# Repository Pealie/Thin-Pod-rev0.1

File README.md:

# Thin-Pod rev 0.1

<p align="left">
  
</p>
<p align="left">
  <strong>OSHWA Certified Open Source Hardware · UK000091</strong><br>
  Certified 28 May 2026 · <a href="https://certification.oshwa.org/uk000091.html">View certification record</a>
</p>

## Overview

Thin-Pod rev 0.1 is a compact analogue vibration-sensing carrier board intended for experimental condition-monitoring work on motors, pumps, fans, gearboxes and similar rotating machinery. The board supports an ADXL1005-based analogue accelerometer signal path and provides protected power entry, a regulated and switched sensor supply, signal conditioning, accessible test points and a mating interface for a commercially supplied Qorvo DWM3001-CDK development board.

The design is published as an open-hardware PCB release: editable KiCad source files, project-local library files, fabrication outputs, bill of materials and verification documentation are provided in this repository.

The release is intentionally bounded: its value lies in producing a reproducible, inspectable measurement endpoint whose power path, signal path, interface assumptions and validation evidence can support later Gateway-side analysis, reporting and evaluation work within a clearly defined certified hardware boundary.

## Certification scope

The OSHWA certification for **Thin-Pod rev 0.1** covers the creator-designed sensor-node carrier PCB and its release documentation.

### Included in scope

* Two-layer Thin-Pod carrier PCB design.
* Protected power-entry path, fuse provision and reverse-polarity protection.
* Regulated 3.3 V power path and PFET-switched accelerometer supply.
* ADXL1005 analogue sensor interface and conditioned signal path.
* Electrical test points for bring-up and measurement.
* Thin-Pod-authored mating interface for a Qorvo DWM3001-CDK.
* Corrected carrier-board ground return for the DWM3001-CDK interface.
* Editable KiCad source files, fabrication outputs, BOM and documentation.

### Outside scope

* The Qorvo DWM3001-CDK itself as open hardware.
* The Analog Devices ADXL1005 device or any vendor evaluation board as open hardware.
* The Pololu S7V8F3 regulator module as open hardware.
* The separately developed Thin-Pod Gateway.
* STM32 NUCLEO-N657X0-Q, ESP32-C6 or Gateway-side hardware.
* Implemented UWB communication, radio firmware or networking.
* Gateway-side DSP, TinyML inference, anomaly detection or predictive-maintenance classification.
* AI-assisted maintenance reporting, structured evidence-bound reports or autonomous maintenance decisions.

The commercial devices used by the board are identified as third-party components; they are not relicensed or represented as creator-designed open hardware.

## System role and infrastructure context

Thin-Pod rev 0.1 is the sensing-node hardware layer within a broader experimental condition-monitoring architecture. Its immediate role is to provide a reproducible, inspectable and electrically verified vibration-measurement endpoint for motors, pumps, fans, gearboxes and similar rotating machinery.

```
Machine / motor / pump
        ↓
Thin-Pod rev 0.1 sensing node
        ↓
ADC / UWB-capable commercial module interface
        ↓
Gateway transport and analysis layer
        ↓
Maintenance telemetry / diagnostic workflow
```

The infrastructure concerns addressed by this release are measurement integrity, power-path robustness, interface definition, third-party component boundaries, traceable validation evidence and manufacturable open-hardware documentation.

Only the Thin-Pod rev 0.1 sensing-node carrier PCB and its release documentation are included in the certified open-hardware scope. The ADC-capable commercial module interface is documented as part of the board design, but the commercial module itself is not claimed as open hardware.

Gateway transport, UWB communications, networking, DSP, TinyML, anomaly detection and maintenance-diagnostic workflows are shown here to clarify the intended system context. They are part of the wider Thin-Pod development direction, but remain outside the certified rev 0.1 hardware release.

This boundary is deliberate. Thin-Pod rev 0.1 is designed to make the physical measurement layer explicit before higher-level interpretation is attempted. Later Gateway or software layers can consume the resulting signal path, but any DSP, anomaly detection, AI-assisted reporting or maintenance recommendation must remain separately implemented, evaluated and documented.

## Functional architecture

```text
Mechanical vibration
        ↓
ADXL1005 analogue accelerometer interface
        ↓
Analogue conditioning / filtered signal node
        ↓
Accessible test point and CDK ADC interface
        ↓
Commercial Qorvo DWM3001-CDK connection
```

Power is arranged as:

```text
RAW_IN → fuse provision → 1N5817 reverse-polarity protection
       → Pololu S7V8F3 regulated 3.3 V rail
       → PFET-switched accelerometer supply
```

## Evidence-chain design intent

Thin-Pod rev 0.1 is intended to support an evidence-chain approach to experimental condition monitoring. The carrier board provides the physical sensing and interface layer; later Gateway-side work may attach acquisition metadata, operating-context records, DSP feature outputs, baseline comparisons and report provenance.

In that wider architecture, the hardware layer should remain distinct from any interpretive software layer. The board records or exposes a vibration signal; it does not itself diagnose machine faults. This separation is important for reproducibility, safety, evaluation and possible future AI-assisted reporting workflows.

## DWM3001-CDK ground-return correction

During bring-up of an earlier pre-release manufactured prototype, the CDK did not establish the assumed functional ground return through the original power-entry arrangement alone. A temporary ground jumper allowed successful electrical bring-up and measurement of the sensor path.

Before freezing the rev 0.1 open-hardware release, the CDK mating interface and carrier-board connection were corrected so that all relevant CDK ground connections resolve directly to the Thin-Pod `GND` net:

```text
J1_2    GND    ─┐
J1_6    GND_1  ─┤
J10_9   GND_2  ─┤
J10_14  GND_3  ─┼── GND
J10_20  GND_4  ─┤
J10_25  GND_5  ─┘
```

The editable source and fabrication outputs in this repository include that correction. The temporary jumper is part of the prototype history and is **not** an assembly requirement for the released rev 0.1 design.

## Validation status

The first manufactured pre-release prototype established that the core sensor-node approach is electrically viable. Measurements made during prototype bring-up included:

|Validation item|Result|Evidence status|
|-|-|-|
|Manufactured PCB inspection and initial assembly|Completed|Documented in bring-up record and images|
|Power-up after temporary CDK ground-return correction|Successful|Documented prototype result|
|Switched accelerometer supply rail|Approximately 3.35 V measured|Documented prototype result|
|Filtered analogue sensor output|Approximately 1.76 V measured at rest|Documented prototype result|
|Mechanical excitation / tap response|Visible on oscilloscope|Documented prototype result|
|Ground-return correction implemented in released KiCad source and Gerbers|Completed|Included in this release|
|Physical re-test of the corrected copper implementation without jumper|To be recorded after manufacture of the corrected release board|Not claimed as completed|

The prototype measurement evidence supports the power and analogue signal-chain design. The corrected ground-return implementation is present in the released design files; it is not represented as physically re-tested until a board manufactured from these release Gerbers has been assembled and measured.

## Repository contents

```text
Thin-Pod-rev0.1/
├── README.md
├── LICENCE-HARDWARE.md
├── LICENCE-DOCUMENTATION.md
│
├── hardware/
│   ├── source/
│   │   ├── Thin-Pod_rev0.1.kicad_pro
│   │   ├── Thin-Pod_rev0.1.kicad_sch
│   │   ├── Thin-Pod_rev0.1.kicad_pcb
│   │   ├── fp-lib-table
│   │   ├── sym-lib-table
│   │   ├── footprints/
│   │   │   └── ThinPod.pretty/
│   │   │       └── ThinPod_DWM3001CDK_Mating_Interface_revA.kicad_mod
│   │   └── symbols/
│   │       └── ThinPod.kicad_sym
│   │
│   ├── fabrication/
│   │   ├── gerbers/
│   │   ├── drills/
│   │   └── Thin-Pod_rev0.1_fabrication_outputs.zip
│   │
│   └── bom/
│       ├── Thin-Pod_rev0.1_BOM.md
│       └── Thin-Pod_rev0.1_BOM.csv
│
├── docs/
│   ├── certification-scope.md
│   ├── third-party-components.md
│   ├── footprint-provenance.md
│   ├── prototype-bring-up-and-release-correction.md
│   ├── design-verification.md
│   └── future-revisions.md
│
├── images/
│   ├── certification/
│   │   └── oshwa-uk000091.png
│   ├── prototype-bring-up/
│   ├── gerber-inspection/
│   └── released-design/
│	└── README.md
│
└── oshwa/
    └── application-record.md
    └── README.md
```

## Design and fabrication files

|Resource|Location|Purpose|
|-|-|-|
|Editable KiCad project, schematic and PCB|[`hardware/source/`](hardware/source/)|Preferred source for modification|
|Project-local footprints and symbols|[`hardware/source/`](hardware/source/)|Portable project dependencies|
|Gerber and drill files|[`hardware/fabrication/`](hardware/fabrication/)|PCB fabrication outputs|
|Bill of materials|[`hardware/bom/`](hardware/bom/)|Assembly and sourcing record|
|Certification and design documentation|[`docs/`](docs/)|Scope, provenance and validation record|
|OSHWA application and certification record|[`oshwa/application-record.md`](oshwa/application-record.md)|Public submission details and certification UID|

The editable KiCad source files are the normative design source. Gerbers and drill files are derived fabrication outputs supplied for convenience and reproducibility.

## Bill of materials

The release BOM covers the Thin-Pod rev 0.1 sensor-node carrier board only. It identifies the fitted PCB components, commercial subassemblies, component values, footprints and sourcing information required to reproduce this release.

The Gateway, Gateway-side radio components, ESP32 networking hardware and analytic processing hardware are not part of this BOM because they are outside the rev 0.1 certification scope.

See:

* [`hardware/bom/Thin-Pod_rev0.1_BOM.md`](hardware/bom/Thin-Pod_rev0.1_BOM.md)
* [`hardware/bom/Thin-Pod_rev0.1_BOM.csv`](hardware/bom/Thin-Pod_rev0.1_BOM.csv)

## Third-party components

Thin-Pod rev 0.1 is an open carrier-board design built around commercially available components. The following items are used or interfaced by the design but are not claimed as open-hardware contributions of this project:

|Component|Function in Thin-Pod rev 0.1|Treatment in this release|
|-|-|-|
|Analog Devices ADXL1005-based accelerometer implementation|Analogue vibration sensing|Commercial third-party component; interface documented|
|Qorvo DWM3001-CDK|Commercial module connected through the pod-side mating interface|Commercial third-party development board; not relicensed|
|Pololu S7V8F3|Regulated 3.3 V supply module|Commercial third-party module|
|ZVP2106A and standard passive/protection components|Power switching and analogue support circuitry|Commercial bought-in components identified in BOM|

Vendor documentation is referenced for sourcing and interface understanding; vendor CAD files, proprietary board layouts and vendor 3D models are not distributed under the Thin-Pod hardware licence.

## CDK mating-interface footprint provenance

The published footprint:

```text
hardware/source/footprints/ThinPod.pretty/
└── ThinPod_DWM3001CDK_Mating_Interface_revA.kicad_mod
```

is a Thin-Pod project-local mating-interface footprint for the commercially supplied DWM3001-CDK. It is intended to describe only the mechanical and electrical connection required by the Thin-Pod carrier PCB.

The release footprint was independently constructed in KiCad using standard connector geometry, publicly available interface information and mechanical verification against a purchased CDK unit. It does not distribute a Qorvo-supplied CAD footprint, CDK PCB design or vendor 3D model.

## Opening and modifying the design

The source design is maintained in KiCad 10.0.1. The project is intended to be portable through project-local symbol and footprint tables.

A reproducible modification workflow is:

1. Open `hardware/source/Thin-Pod_rev0.1.kicad_pro` in KiCad 10.0.1 or a compatible later version.
2. Confirm that project-local symbol and footprint libraries resolve through `sym-lib-table` and `fp-lib-table`.
3. Run schematic ERC and PCB DRC before fabrication.
4. Regenerate Gerber and drill outputs after any accepted design change.
5. Inspect copper, solder mask, silkscreen, board outline and drill alignment in KiCad Gerber Viewer before ordering.

## Documentation and verification record

|Document|Content|
|-|-|
|[`docs/certification-scope.md`](docs/certification-scope.md)|Formal inclusion and exclusion boundary for certification|
|[`docs/third-party-components.md`](docs/third-party-components.md)|Commercial component and vendor-material notice|
|[`docs/footprint-provenance.md`](docs/footprint-provenance.md)|Origin and verification of the CDK mating-interface footprint|
|[`docs/prototype-bring-up-and-release-correction.md`](docs/prototype-bring-up-and-release-correction.md)|Prototype test result and ground-return design correction|
|[`docs/design-verification.md`](docs/design-verification.md)|Electrical and fabrication verification record|
|[`docs/future-revisions.md`](docs/future-revisions.md)|Items explicitly outside this release|

## Licensing

|Material|Licence|File|
|-|-|-|
|Creator-designed hardware source, including schematics, PCB layout and Thin-Pod-authored footprint files|CERN Open Hardware Licence Version 2 — Weakly Reciprocal (`CERN-OHL-W-2.0`)|[`LICENCE-HARDWARE.md`](LICENCE-HARDWARE.md)|
|Creator-authored documentation, diagrams and photographs|Creative Commons Attribution 4.0 International (`CC-BY-4.0`)|[`LICENCE-DOCUMENTATION.md`](LICENCE-DOCUMENTATION.md)|
|Software / firmware|None required or supplied for the certified rev 0.1 hardware scope|Not applicable|

Commercial components, vendor documentation and any third-party intellectual property remain subject to their respective owners' terms and are not covered by the Thin-Pod licences. The OSHWA certification mark is used to identify this certified release and is not relicensed as Thin-Pod documentation.

## OSHWA certification record

**Thin-Pod rev 0.1 is certified open source hardware under OSHWA UID UK000091.** The certification mark displayed near the top of this README identifies this specific certified release and links to the public OSHWA record.

|Field|Value|
|-|-|
|Project name|Thin-Pod|
|Project version|0.1|
|Primary project type|Electronics|
|Certification scope|Vibration-sensor node carrier PCB|
|Certification date|28 May 2026|
|Hardware licence|CERN-OHL-W-2.0|
|Documentation licence|CC-BY-4.0|
|Software licence|No software required or supplied for the certified hardware scope|
|OSHWA UID|UK000091|
|Official record|[certification.oshwa.org/uk000091](https://certification.oshwa.org/uk000091.html)|

The certification UID and matching mark are retained in this README and in [`oshwa/application-record.md`](oshwa/application-record.md), keeping the boundary of the certified rev 0.1 release explicit.

## Safety and regulatory note

Thin-Pod rev 0.1 is experimental sensing hardware. It has not been certified for installation on safety-critical machinery, hazardous environments or regulated industrial monitoring applications. Appropriate isolation, current-limited bench testing, secure mechanical mounting and safe working practices are required during evaluation.

This open-hardware release does not imply EMC, radio, electrical-safety or product-regulatory approval. Any commercially supplied radio or development module remains subject to its own vendor documentation and applicable regulatory conditions.

## References

* [Thin-Pod OSHWA Certification Record — UK000091](https://certification.oshwa.org/uk000091.html)
* [OSHWA Certification Mark Usage Guide](https://certification.oshwa.org/mark-usage.html)
* [OSHWA Certification Requirements](https://certification.oshwa.org/requirements.html)
* [OSHWA Certification Documentation Process](https://certification.oshwa.org/process/documentation.html)
* [OSHWA Certification Application](https://application.oshwa.org/apply)
* [Qorvo DWM3001-CDK product page](https://www.qorvo.com/products/p/DWM3001CDK)
* [Analog Devices ADXL1005 product page](https://www.analog.com/en/products/adxl1005.html)

---

**Thin-Pod rev 0.1** is a deliberately bounded first open-hardware release: a documented vibration-sensor node PCB with a clear commercial-module boundary, an independently authored interface footprint, traceable prototype-validation evidence and a release design that incorporates the principal lesson discovered during bring-up.

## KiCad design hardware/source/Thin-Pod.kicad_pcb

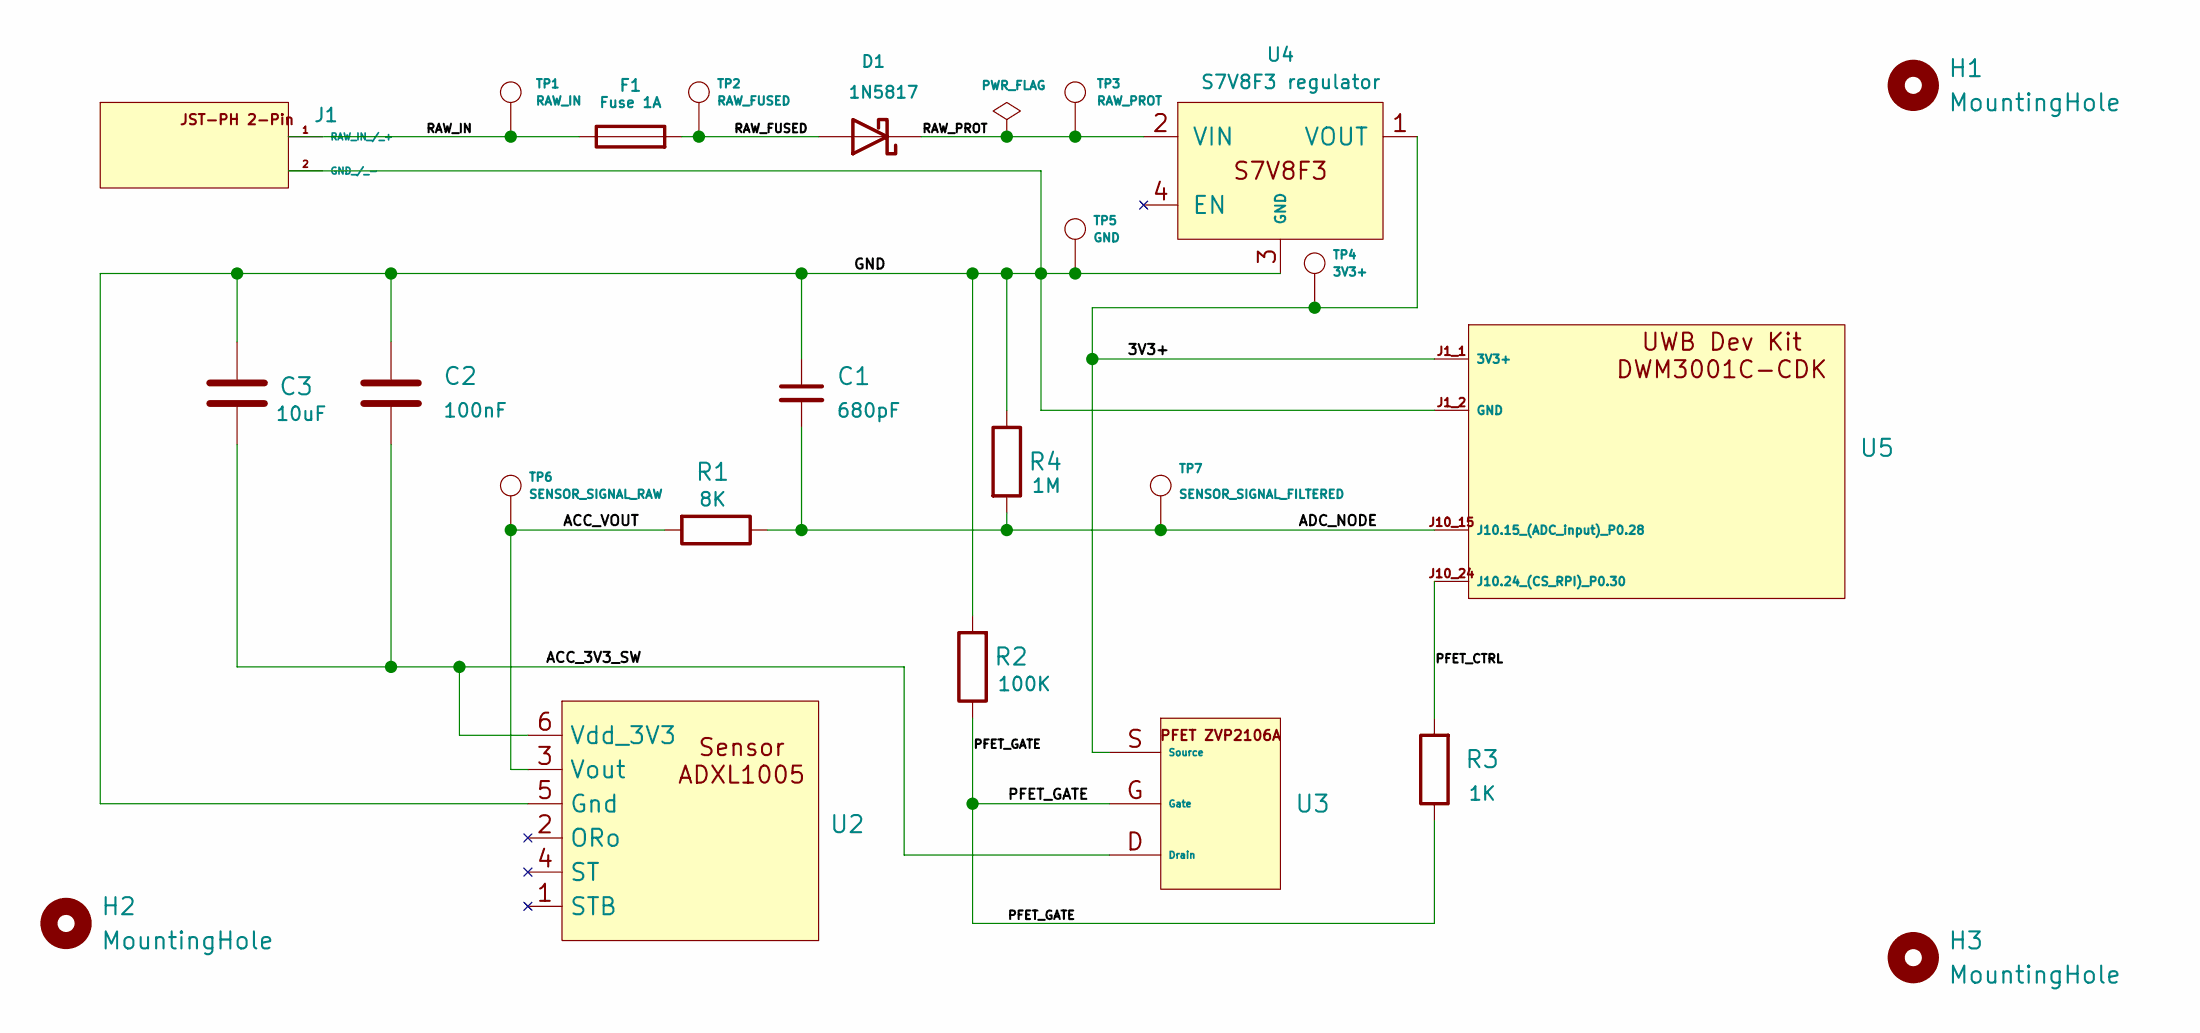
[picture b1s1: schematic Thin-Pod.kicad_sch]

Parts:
C1: 680pF; C_Disc_D3.0mm_W1.6mm_P2.50mm
C2: 100nF; C_Disc_D3.0mm_W1.6mm_P2.50mm
C3: 10uF; C_Disc_D5.0mm_W2.5mm_P5.00mm
D1: 1N5817; D_DO-41_SOD81_P10.16mm_Horizontal
F1: Fuse 1A; Fuseholder_Littelfuse_445_030_series_5x20mm
H1, H2, H3: MountingHole; MountingHole_2.7mm_M2.5
J1: JST_PH_S2B-PH-K_1x02_P2.00mm_Horizontal
R1: 8K; R_Axial_DIN0207_L6.3mm_D2.5mm_P7.62mm_Horizontal
R2: 100K; R_Axial_DIN0207_L6.3mm_D2.5mm_P7.62mm_Horizontal
R3: 1K; R_Axial_DIN0207_L6.3mm_D2.5mm_P7.62mm_Horizontal
R4: 1M; R_Axial_DIN0207_L6.3mm_D2.5mm_P7.62mm_Horizontal
TP1: RAW_IN; TestPoint_THTPad_D1.5mm_Drill0.7mm
TP2: RAW_FUSED; TestPoint_THTPad_D1.5mm_Drill0.7mm
TP3: RAW_PROT; TestPoint_THTPad_D1.5mm_Drill0.7mm
TP4: 3V3+; TestPoint_THTPad_D1.5mm_Drill0.7mm
TP5: GND; TestPoint_THTPad_D1.5mm_Drill0.7mm
TP6: SENSOR_SIGNAL_RAW; TestPoint_THTPad_D1.5mm_Drill0.7mm
TP7: SENSOR_SIGNAL_FILTERED; TestPoint_THTPad_D1.5mm_Drill0.7mm
U2: AnalogDevices_EVAL-ADXL100xZ_20p35mm
U3: PFET_ZVP2106A_GSD_THT
U4: S7V8F3 regulator; Pololu_S7V8F3_S7V8x_Module
U5: DWM3001C-CDK; MODULE_DWM3001CDK

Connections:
/3V3+: TP4.1 (1_1), U3.S (Source), U4.1 (VOUT), U5.J1_1 (3V3+)
/ACC_3V3_SW: C2.2, C3.2, U2.6 (Vdd_3V3), U3.D (Drain)
/ACC_VOUT: R1.2, TP6.1 (1_1), U2.3 (Vout)
/ADC_NODE: C1.2, R1.1, R4.2, TP7.1 (1_1), U5.J10_15 (J10.15_(ADC_input)_P0.28)
/GND: C1.1, C2.1, C3.1, J1.2 (GND_/_-), R2.2, R4.1, TP5.1 (1_1), U2.5 (Gnd), U4.3 (GND), U5.J1_2 (GND), U5.J10_6, U5.J10_9, U5.J10_14, U5.J10_20, U5.J10_25
/PFET_CTRL: R3.2, U5.J10_24 (J10.24_(CS_RPI)_P0.30)
/PFET_GATE: R2.1, R3.1, U3.G (Gate)
/RAW_FUSED: D1.2 (A), F1.2, TP2.1 (1_1)
/RAW_IN: F1.1, J1.1 (RAW_IN_/_+), TP1.1 (1_1)
/RAW_PROT: D1.1 (K), TP3.1 (1_1), U4.2 (VIN)

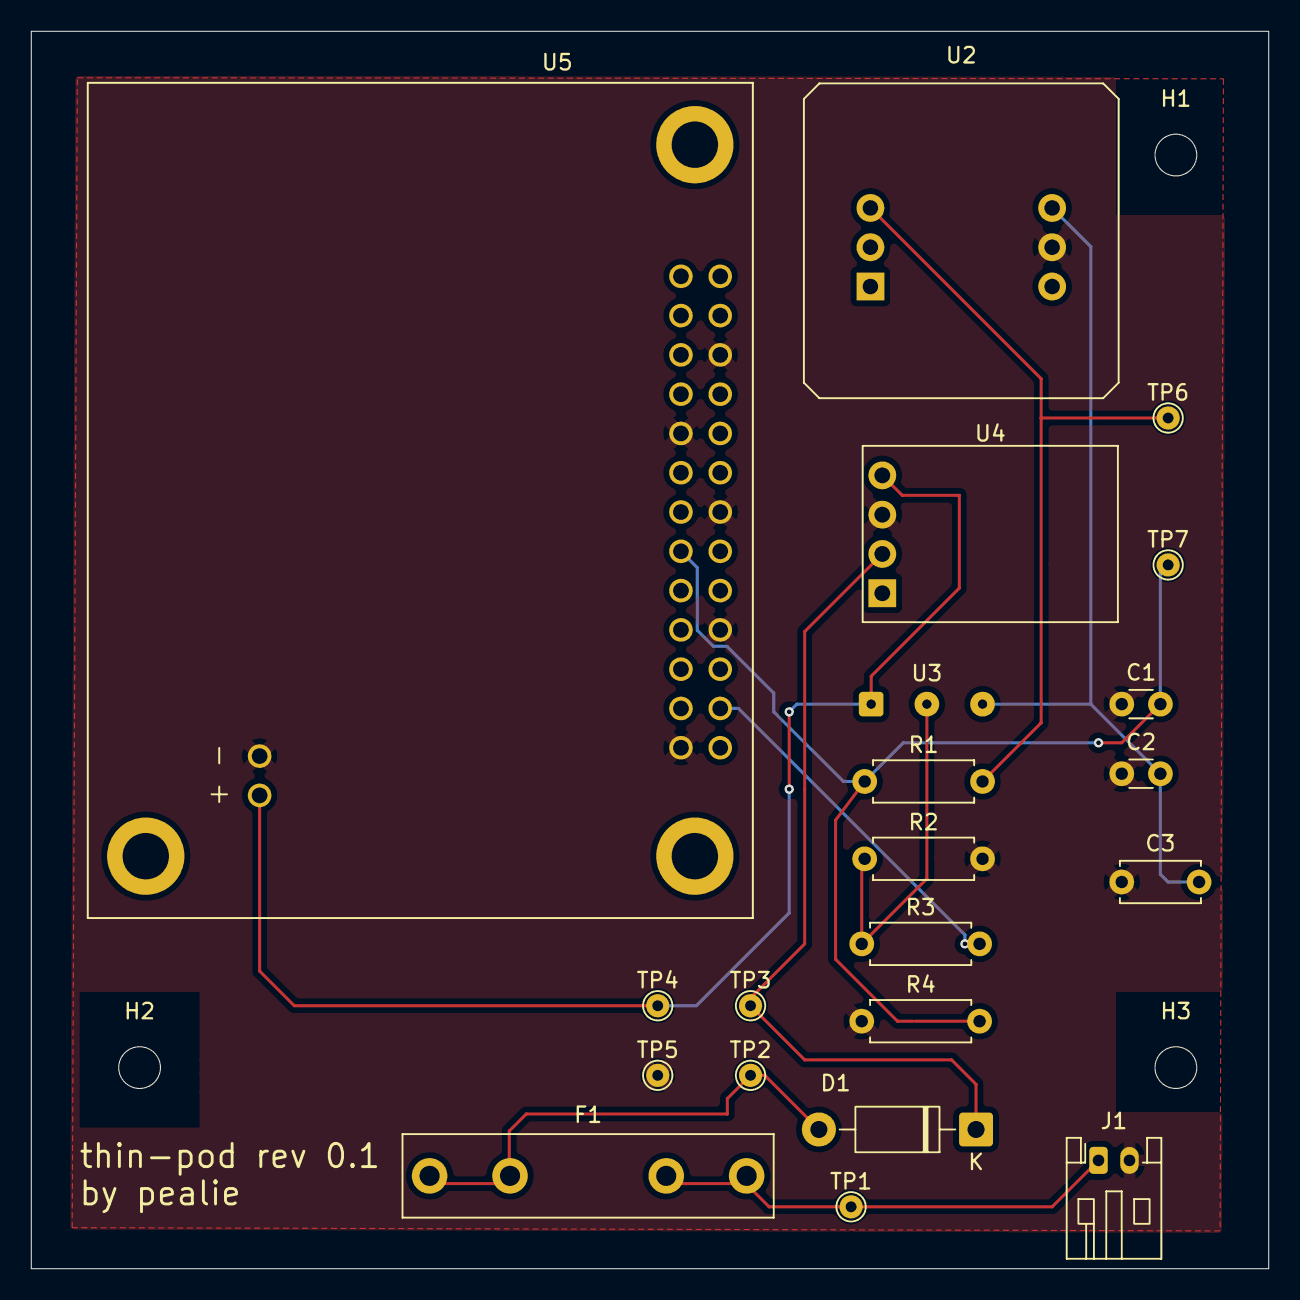
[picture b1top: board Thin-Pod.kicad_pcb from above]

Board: 2 copper layers, 80.0 x 80.0 mm, 24 parts (0 on the bottom side), 10 nets.

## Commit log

2026-05-26 Add rev 0.1 BOM files and correct README links
2026-06-23 Add documentation index
2026-06-25 Restore OSHWA certification mark used by README
